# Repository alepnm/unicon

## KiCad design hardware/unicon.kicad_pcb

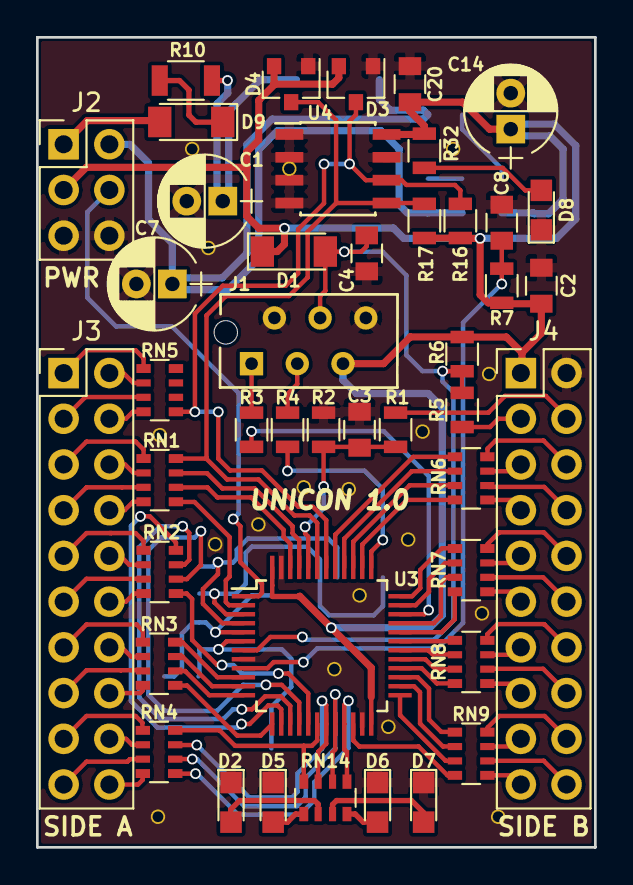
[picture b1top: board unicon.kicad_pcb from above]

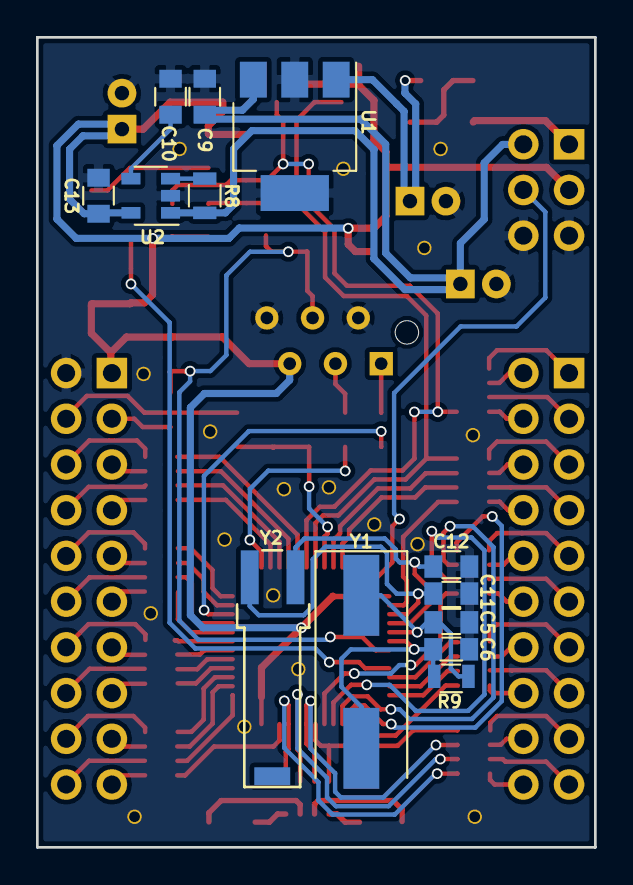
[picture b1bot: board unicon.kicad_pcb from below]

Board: 2 copper layers, 31.0 x 45.0 mm, 57 parts (13 on the bottom side), 96 nets.

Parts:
C1, C7, C14: 100uFx16V; CP_Radial_D5.0mm_P2.00mm
C2, C3, C4, C8, C9, C10, C13, C20: 100nF; C_0805
C5, C6, C11, C12: 15pF; C_0805
D1, D9: BAS32; D_MiniMELF
D2: LED2; LED_0805
D3, D4: BAT54S; SOT-23
D5: LED5; LED_0805
D6: LED6; LED_0805
D7: LED7; LED_0805
D8: POWER; LED_0805
J1: PROG; ISP_SWD_Connector
J2: PWR; Pin_Header_Straight_2x03_Pitch2.54mm
J3: SIDE A; Pin_Header_Straight_2x10_Pitch2.54mm
J4: SIDE B; Pin_Header_Straight_2x10_Pitch2.54mm
R1, R7: 120R; R_0805
R2, R32: 10k; R_0805
R3, R4, R5: 47R; R_0805
R6, R8: 15k; R_0805
R9: 1M2; R_0805
R10: 120R; R_1206
R16, R17: 4.7k; R_0805
RN1, RN2, RN3, RN4, RN5, RN6, RN7, RN8, RN9: RN_100R_5%; RN1206
RN14: 100R; RN1206
U1: LM340MP-5.0; LM340_SOT-223
U2: SIP21106-3.3; SOT-23-5
U3: STM32F051C8Tx; LQFP-48_7x7mm_Pitch0.5mm
U4: AT24C16; SOIC-8_3.9x4.9mm_Pitch1.27mm
Y1: 8MHz; Crystal_SMD_HC49-SD
Y2: 32768 Hz; Crystal_32768_horizontzl

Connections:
/3VDC: C2.1, C13.1, C14.1, C20.1, D1.1, D3.2, D4.2, J1.5, J2.3, J4.1, R6.2, R7.1, R16.2, R17.2, R32.1, U2.5, U3.24, U3.48, U4.8
/5VDC: C7.1, C9.1, J2.2, R8.2, U1.3, U2.1
/12VDC: D9.2, J2.1
/A0: RN3.7, U3.10
/A1: RN3.5, U3.11
/A2: RN3.3, U3.12
/A3: RN3.1, U3.13
/A4: RN2.7, U3.14
/A5: RN2.5, U3.15
/A6: RN2.3, U3.16
/A7: RN2.1, U3.17
/A8: RN8.5, U3.29
/A9: RN8.3, U3.30
/A10: RN8.1, U3.31
/A11: RN7.7, U3.32
/A12: RN7.5, U3.33
/A15: RN6.7, U3.38
/B0: RN4.7, RN14.7, U3.18
/B1: RN4.5, RN14.5, U3.19
/B2: RN4.3, RN14.3, U3.20
/B3: RN6.5, U3.39
/B4: RN6.3, U3.40
/B5: RN6.1, U3.41
/B6: D3.3, R16.1, RN5.1, U3.42, U4.6
/B7: D4.3, R17.1, RN1.7, U3.43, U4.5
/B8: RN1.5, U3.45
/B9: RN1.3, U3.46
/B10: RN4.1, RN14.1, U3.21
/B11: RN9.7, U3.22
/B12: RN9.5, U3.25
/B13: RN9.3, U3.26
/B14: RN9.1, U3.27
/B15: RN8.7, U3.28
/BOOT0: J4.4, R1.2
/BT0: C3.1, R1.1, R2.2, U3.44
/C13: RN1.1, U3.2
/COM: C1.2, C2.2, C3.2, C4.2, C5.2, C6.2, C7.2, C8.2, C9.2, C10.2, C11.2, C12.2, C13.2, C14.2, C20.2, D2.1, D3.1, D4.1, D5.1, D6.1, D7.1, D8.1, J1.2, J1.6, J2.5, J2.6, J4.2, R2.1, U1.2, U2.2, U3.8, U3.23, U3.47, U4.1, U4.2, U4.3, U4.4, U4.7
/F6: RN7.3, U3.35
/F7: RN7.1, U3.36
/J3.1: J3.1, RN5.8
/J3.2: J3.2, RN5.6
/J3.3: J3.3, RN5.4
/OSC32_I: C11.1, U3.3, Y2.1
/OSC32_O: C12.1, U3.4, Y2.2
/OSCIN: C5.1, R9.1, U3.5, Y1.1
/OSCOUT: C6.1, R9.2, U3.6, Y1.2
/PA0: J3.13, RN3.8
/PA1: J3.14, RN3.6
/PA2: J3.15, RN3.4
/PA3: J3.16, RN3.2
/PA4: J3.9, RN2.8
/PA5: J3.10, RN2.6
/PA6: J3.11, RN2.4
/PA7: J3.12, RN2.2
/PA8: J4.16, RN8.6
/PA9: J4.13, RN8.4
/PA10: J4.14, RN8.2
/PA11: J4.11, RN7.8
/PA12: J4.12, RN7.6
/PA15: J4.7, RN6.8
/PB0: J3.17, RN4.8
/PB1: J3.18, RN4.6
/PB2: J3.19, RN4.4
/PB3: J4.8, RN6.6
/PB4: J4.5, RN6.4
/PB5: J4.6, RN6.2
/PB6: J3.4, RN5.2
/PB7: J3.5, RN1.8
/PB8: J3.6, RN1.6
/PB9: J3.7, RN1.4
/PB10: J3.20, RN4.2
/PB11: J4.19, RN9.8
/PB12: J4.20, RN9.6
/PB13: J4.17, RN9.4
/PB14: J4.18, RN9.2
/PB15: J4.15, RN8.8
/PC13: J3.8, RN1.2
/PF6: J4.9, RN7.4
/PF7: J4.10, RN7.2
/SWCLK: R4.2, U3.37
/SWDIO: R3.2, U3.34
/VBAT: J2.4, U3.1
/VDDA: C8.1, R7.2, U3.9
/~NRST: C4.1, D1.2, J1.4, R5.1, R6.1, U3.7
/~NRSTP: J4.3, R5.2
unnamed: C1.1, R10.2, U1.1
unnamed: C10.1, U2.4
unnamed: D2.2, RN14.6
unnamed: D5.2, RN14.8
unnamed: D6.2, RN14.2
unnamed: D7.2, RN14.4
unnamed: D8.2, R32.2
unnamed: D9.1, R10.1
unnamed: J1.1, R3.1
unnamed: J1.3, R4.1
unnamed: R8.1, U2.3

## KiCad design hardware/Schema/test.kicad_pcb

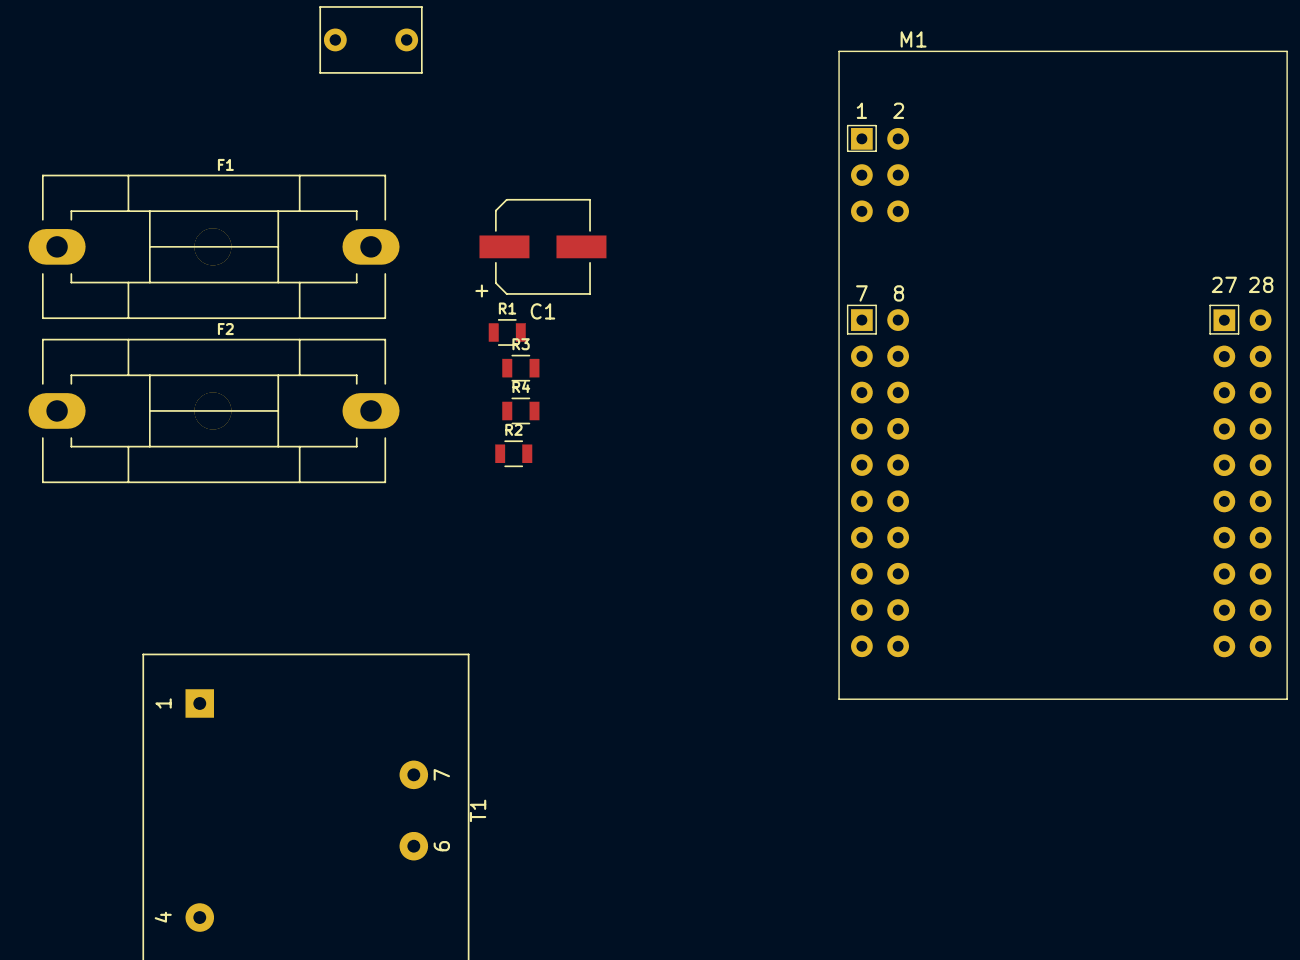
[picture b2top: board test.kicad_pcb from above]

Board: 2 copper layers, 10 parts (0 on the bottom side), 8 nets, no tracks yet.

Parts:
C1: 100uFx16V; CP_Elec_6.3x5.7
F1: 1A; Fuseholder5x20_horiz_SemiClosed_Casing10x25mm
F2: 5A; Fuseholder5x20_horiz_SemiClosed_Casing10x25mm
M1: unicon_v1
R1: 1k; R_0805
R2: 120R; R_0805
R3, R4: Rx; R_0805
T1: Transformer_TEZ_22x24_6V; Transformer_Breve_TEZ-22x24_6V
TH1: 250/120mA; C_Rect_L7.0mm_W4.5mm_P5.00mm

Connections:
/AC2: F1.1, F2.1
/AC2A: T1.4, TH1.2
/AIN: R1.2, R2.2
/VREF: M1.27, R3.2
GND: C1.2, M1.4, M1.5, M1.6, M1.28, R4.2
unnamed: C1.1, R2.1, R3.1, R4.1, T1.7
unnamed: F1.2, TH1.1
unnamed: R1.1, T1.6

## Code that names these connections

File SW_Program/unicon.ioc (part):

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Mcu.Name=STM32F051C6Tx
Mcu.Package=LQFP48
Mcu.UserName=STM32F051C6Tx
PA0.GPIOParameters=GPIO_PuPd,GPIO_Mode
PA0.GPIO_Mode=GPIO_MODE_INPUT
PA0.GPIO_PuPd=GPIO_NOPULL
PA0.Signal=GPIO_Input
PA1.GPIOParameters=GPIO_PuPd,GPIO_Mode
PA1.GPIO_Mode=GPIO_MODE_INPUT
PA1.GPIO_PuPd=GPIO_NOPULL
PA1.Signal=GPIO_Input
PA10.Mode=Asynchronous
PA10.Signal=USART1_RX
PA11.GPIOParameters=GPIO_Speed,PinState,GPIO_PuPd,GPIO_ModeDefaultOutputPP
PA11.GPIO_ModeDefaultOutputPP=GPIO_MODE_OUTPUT_PP
PA11.GPIO_PuPd=GPIO_NOPULL
PA11.GPIO_Speed=GPIO_SPEED_FREQ_LOW
PA11.PinState=GPIO_PIN_RESET
PA11.Signal=GPIO_Output
PA12.Mode=Hardware Flow Control (RS485)
PA12.Signal=USART1_DE
PA13.Mode=Serial_Wire
PA13.Signal=SYS_SWDIO
PA14.Mode=Serial_Wire
PA14.Signal=SYS_SWCLK
PA15.GPIOParameters=GPIO_PuPd,GPIO_Mode
PA15.GPIO_Mode=GPIO_MODE_INPUT
PA15.GPIO_PuPd=GPIO_NOPULL
PA15.Signal=GPIO_Input
PA2.GPIOParameters=GPIO_PuPd,GPIO_Mode
PA2.GPIO_Mode=GPIO_MODE_INPUT
PA2.GPIO_PuPd=GPIO_NOPULL
PA2.Signal=GPIO_Input
PA3.GPIOParameters=GPIO_PuPd,GPIO_Mode
PA3.GPIO_Mode=GPIO_MODE_INPUT
PA3.GPIO_PuPd=GPIO_NOPULL
PA3.Signal=GPIO_Input
PA4.GPIOParameters=GPIO_PuPd,GPIO_Mode
PA4.GPIO_Mode=GPIO_MODE_INPUT
PA4.GPIO_PuPd=GPIO_NOPULL
PA4.Signal=GPIO_Input
PA5.GPIOParameters=GPIO_Speed,GPIO_PuPd,GPIO_Mode
PA5.GPIO_Mode=GPIO_MODE_AF_PP
PA5.GPIO_PuPd=GPIO_NOPULL
PA5.GPIO_Speed=GPIO_SPEED_FREQ_HIGH
PA5.Mode=Full_Duplex_Master
PA5.Signal=SPI1_SCK
PA6.GPIOParameters=GPIO_Speed,GPIO_PuPd,GPIO_Mode
PA6.GPIO_Mode=GPIO_MODE_AF_PP
PA6.GPIO_PuPd=GPIO_NOPULL
PA6.GPIO_Speed=GPIO_SPEED_FREQ_HIGH
PA6.Mode=Full_Duplex_Master
PA6.Signal=SPI1_MISO
PA7.GPIOParameters=GPIO_Speed,GPIO_PuPd,GPIO_Mode
PA7.GPIO_Mode=GPIO_MODE_AF_PP
PA7.GPIO_PuPd=GPIO_NOPULL
PA7.GPIO_Speed=GPIO_SPEED_FREQ_HIGH
PA7.Mode=Full_Duplex_Master
PA7.Signal=SPI1_MOSI
PA8.GPIOParameters=GPIO_PuPd,GPIO_Mode
PA8.GPIO_Mode=GPIO_MODE_INPUT
PA8.GPIO_PuPd=GPIO_NOPULL
PA8.Signal=GPIO_Input
PA9.Mode=Asynchronous
PA9.Signal=USART1_TX
PB0.GPIOParameters=GPIO_PuPd,GPIO_Mode
PB0.GPIO_Mode=GPIO_MODE_INPUT
PB0.GPIO_PuPd=GPIO_NOPULL
PB0.Signal=GPIO_Input
PB1.GPIOParameters=GPIO_PuPd,GPIO_Mode
PB1.GPIO_Mode=GPIO_MODE_INPUT
PB1.GPIO_PuPd=GPIO_NOPULL
PB1.Signal=GPIO_Input
PB10.GPIOParameters=GPIO_PuPd,GPIO_Mode
PB10.GPIO_Mode=GPIO_MODE_INPUT
PB10.GPIO_PuPd=GPIO_NOPULL
PB10.Signal=GPIO_Input
PB11.GPIOParameters=GPIO_PuPd,GPIO_Mode
PB11.GPIO_Mode=GPIO_MODE_INPUT
PB11.GPIO_PuPd=GPIO_NOPULL
PB11.Signal=GPIO_Input
PB12.GPIOParameters=GPIO_Speed,PinState,GPIO_PuPd,GPIO_ModeDefaultOutputPP
PB12.GPIO_ModeDefaultOutputPP=GPIO_MODE_OUTPUT_PP
PB12.GPIO_PuPd=GPIO_NOPULL
PB12.GPIO_Speed=GPIO_SPEED_FREQ_LOW
PB12.PinState=GPIO_PIN_RESET
PB12.Signal=GPIO_Output
PB13.GPIOParameters=GPIO_Speed,PinState,GPIO_PuPd,GPIO_ModeDefaultOutputPP
PB13.GPIO_ModeDefaultOutputPP=GPIO_MODE_OUTPUT_PP
PB13.GPIO_PuPd=GPIO_NOPULL
PB13.GPIO_Speed=GPIO_SPEED_FREQ_LOW
PB13.PinState=GPIO_PIN_RESET
PB13.Signal=GPIO_Output
PB14.GPIOParameters=GPIO_PuPd,GPIO_Mode
PB14.GPIO_Mode=GPIO_MODE_INPUT
PB14.GPIO_PuPd=GPIO_NOPULL
PB14.Signal=GPIO_Input
PB15.GPIOParameters=GPIO_PuPd,GPIO_Mode
PB15.GPIO_Mode=GPIO_MODE_INPUT
PB15.GPIO_PuPd=GPIO_NOPULL
PB15.Signal=GPIO_Input
PB2.GPIOParameters=GPIO_PuPd,GPIO_Mode
PB2.GPIO_Mode=GPIO_MODE_INPUT
PB2.GPIO_PuPd=GPIO_NOPULL
PB2.Signal=GPIO_Input
PB3.GPIOParameters=GPIO_PuPd,GPIO_Mode
PB3.GPIO_Mode=GPIO_MODE_INPUT
PB3.GPIO_PuPd=GPIO_NOPULL
PB3.Signal=GPIO_Input
PB4.GPIOParameters=GPIO_PuPd,GPIO_Mode
PB4.GPIO_Mode=GPIO_MODE_INPUT
PB4.GPIO_PuPd=GPIO_NOPULL
PB4.Signal=GPIO_Input
PB5.GPIOParameters=GPIO_PuPd,GPIO_Mode
PB5.GPIO_Mode=GPIO_MODE_INPUT
PB5.GPIO_PuPd=GPIO_NOPULL
PB5.Signal=GPIO_Input
PB6.Mode=I2C
PB6.Signal=I2C1_SCL
PB7.Mode=I2C
PB7.Signal=I2C1_SDA
PB9.Signal=S_TIM17_CH1
PC13.GPIOParameters=GPIO_PuPd,GPIO_Mode
PC13.GPIO_Mode=GPIO_MODE_INPUT
PC13.GPIO_PuPd=GPIO_NOPULL
PC13.Signal=GPIO_Input
PC14-OSC32_IN.Mode=LSE-External-Oscillator
PC14-OSC32_IN.Signal=RCC_OSC32_IN
PC15-OSC32_OUT.Mode=LSE-External-Oscillator
PC15-OSC32_OUT.Signal=RCC_OSC32_OUT
PF0-OSC_IN.Mode=HSE-External-Oscillator
PF0-OSC_IN.Signal=RCC_OSC_IN
PF1-OSC_OUT.Mode=HSE-External-Oscillator
PF1-OSC_OUT.Signal=RCC_OSC_OUT
PF6.GPIOParameters=GPIO_Speed,PinState,GPIO_PuPd,GPIO_ModeDefaultOutputPP
PF6.GPIO_ModeDefaultOutputPP=GPIO_MODE_OUTPUT_PP
PF6.GPIO_PuPd=GPIO_NOPULL
PF6.GPIO_Speed=GPIO_SPEED_FREQ_LOW
PF6.PinState=GPIO_PIN_RESET
PF6.Signal=GPIO_Output
PF7.GPIOParameters=GPIO_PuPd,GPIO_Mode
PF7.GPIO_Mode=GPIO_MODE_INPUT
PF7.GPIO_PuPd=GPIO_NOPULL
PF7.Signal=GPIO_Input
RCC.SYSCLKFreq_VALUE=48000000
RCC.SYSCLKSource=RCC_SYSCLKSOURCE_PLLCLK
board=unicon

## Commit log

2018-07-20 pradine inicializacija
2018-07-22 pcb paruosimas, schemos pataisymai
2018-07-23 sugeneruoti gerberiai
2018-07-26 kodo ruosinio paruosimas. aprasyti LEDu defainai
2018-07-26 sutvarkyta modbus biblioteka
2018-07-26 prijungta eeprom_iic biblioteka
2018-07-26 tarpinis kommitas
2018-08-10 atskiriame sluoksnyje, kad galima butu atspausdinti, suzymeti visi kontaktai
2018-08-29 pervadinti sviesos diodai
2018-10-04 vbat atjungtas nuo 3vdc ir isvestas i J1 jungti
2018-10-10 alex 20181009
2018-10-12 20181012
2018-10-12 3d ruosimas
2019-02-01 sukurtas pinout failas
2019-02-01 pertvarkyta projekto direktorija
2019-03-21 isvestas i isore VBAT
